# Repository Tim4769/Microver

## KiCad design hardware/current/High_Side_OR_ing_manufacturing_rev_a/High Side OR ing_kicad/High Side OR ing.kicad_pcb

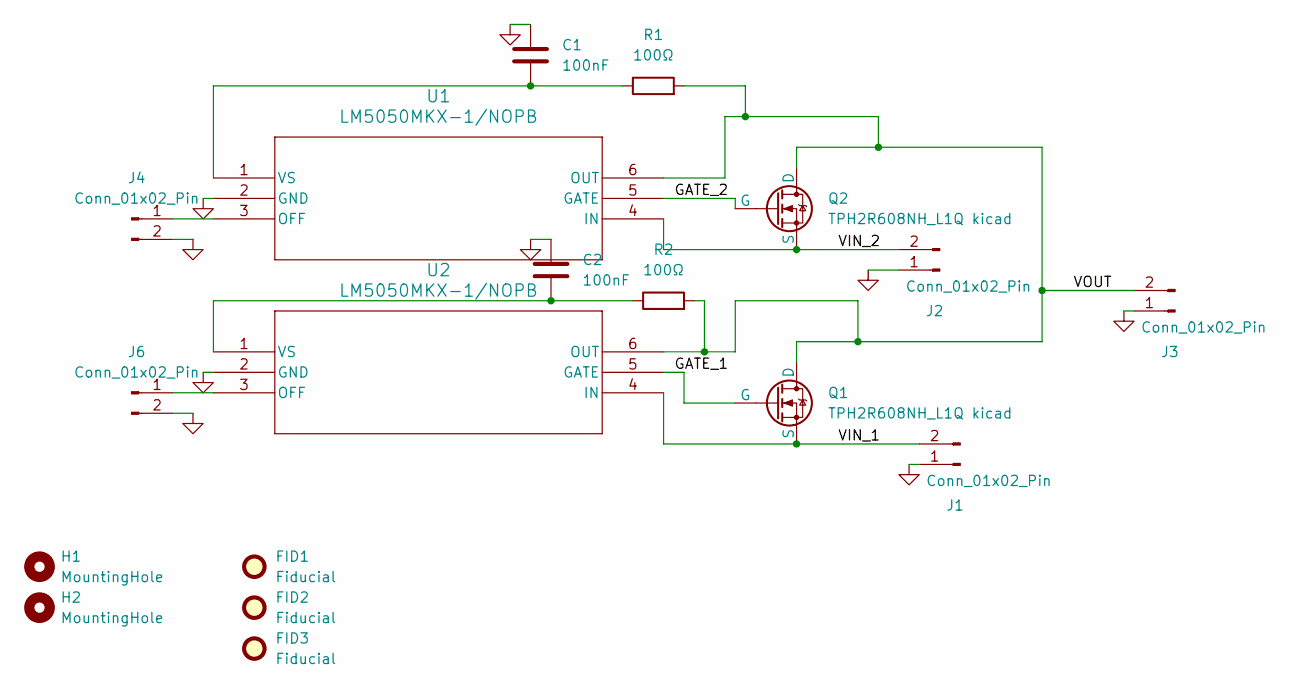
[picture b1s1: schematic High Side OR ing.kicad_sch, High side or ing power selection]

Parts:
C1, C2: 100nF; C_0805_2012Metric; JLCPCB manufactur number C28233
FID1, FID2, FID3: Fiducial; Fiducial_0.5mm_Mask1.5mm
H1, H2: MountingHole; MountingHole_3.2mm_M3
J1, J2, J3: Conn_01x02_Pin; TerminalBlock_MetzConnect_Type011_RT05502HBLC_1x02_P5.00mm_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
J4, J6: Conn_01x02_Pin; PinHeader_1x02_P2.54mm_Vertical
Q1, Q2: TPH2R608NH_L1Q kicad; SOP Advance_TOS; JLCPCB manufactur number C5379811
R1, R2: 100Ω; C_0603_1608Metric; JLCPCB manufactur number C22775
U1, U2: LM5050MKX-1/NOPB; MK06A; JLCPCB manufactur number C473393

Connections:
/GATE_1: Q1.4 (G), U2.5 (GATE)
/GATE_2: Q2.4 (G), U1.5 (GATE)
/VIN_1: J1.2, Q1.1 (S), Q1.2 (S), Q1.3 (S), U2.4 (IN)
/VIN_2: J2.2, Q2.1 (S), Q2.2 (S), Q2.3 (S), U1.4 (IN)
/VOUT: J3.2, Q1.5 (D), Q1.6 (D), Q1.7 (D), Q1.8 (D), Q2.5 (D), Q2.6 (D), Q2.7 (D), Q2.8 (D), R1.2, R2.2, U1.6 (OUT), U2.6 (OUT)
GND: C1.1, C2.1, J1.1, J2.1, J3.1, J4.2, J6.2, U1.2 (GND), U2.2 (GND)
unnamed: J4.1, U1.3 (OFF)
unnamed: J6.1, U2.3 (OFF)
unnamed: C1.2, R1.1, U1.1 (VS)
unnamed: C2.2, R2.1, U2.1 (VS)

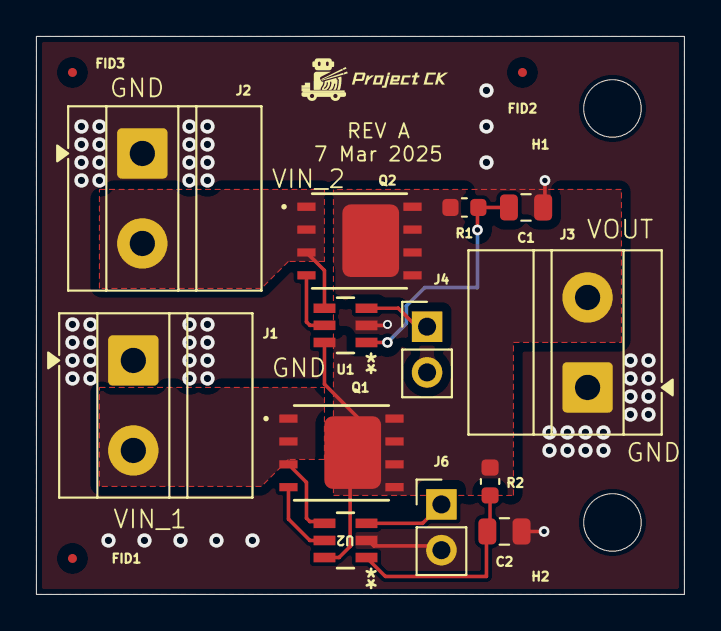
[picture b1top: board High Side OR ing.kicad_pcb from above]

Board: 4 copper layers, 36.0 x 31.0 mm, 18 parts (0 on the bottom side), 10 nets.

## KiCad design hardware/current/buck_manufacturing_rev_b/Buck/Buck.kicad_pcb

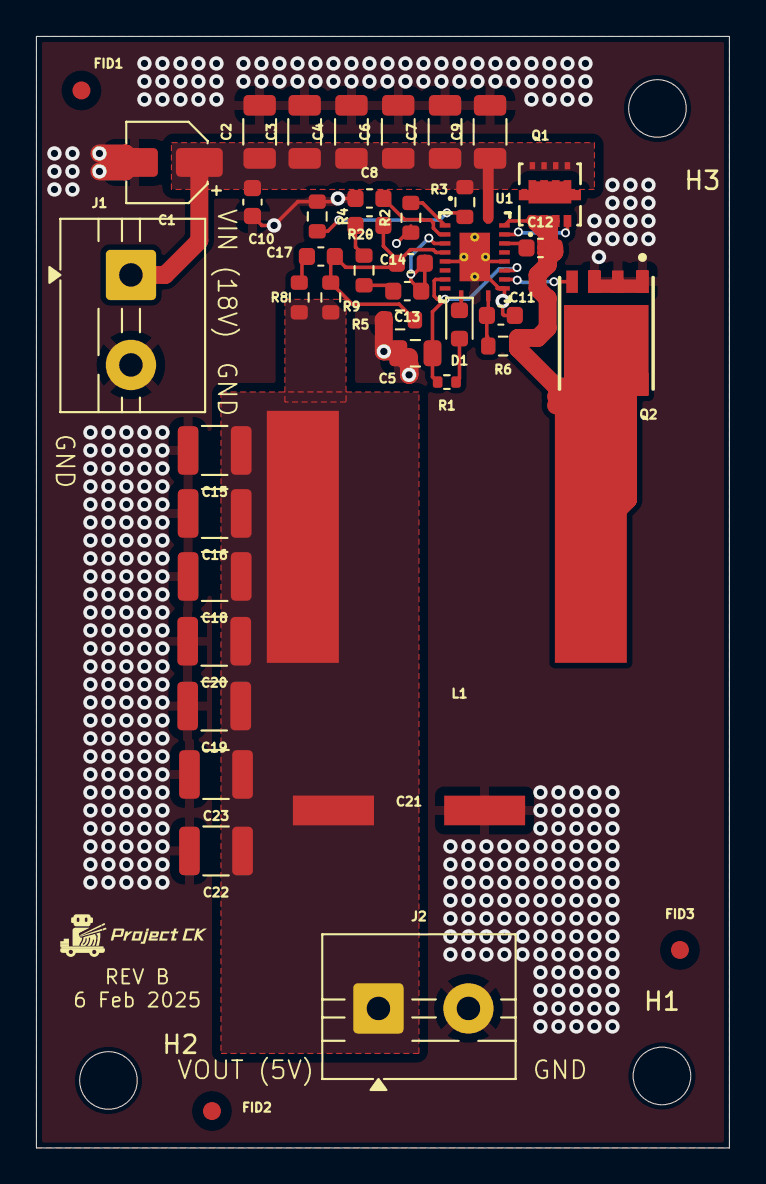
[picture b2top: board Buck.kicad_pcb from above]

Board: 4 copper layers, 38.5 x 61.8 mm, 46 parts (0 on the bottom side), 19 nets.

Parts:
C1: 220 uF; CP_Elec_4x5.4
C2, C3, C4, C6, C7, C9: 4.7 uF; C_1206_3216Metric
C5: 2.2 μF; C_0805_2012Metric
C8: 1uF; C_0603_1608Metric
C10, C12: 0.1 μF; C_0603_1608Metric
C11: 10 pF; C_0603_1608Metric
C13: 4.7nF; C_0603_1608Metric
C14: 68pF; C_0603_1608Metric
C15, C16, C18, C19, C20, C22, C23: 47 μF; C_1210_3225Metric
C17: 2.7nF; C_0603_1608Metric
C21: 680 µF; MA35V680M10X13
D1: R LED; LED_0603_1608Metric
FID1, FID2, FID3: Fiducial; Fiducial_1mm_Mask2mm
H1, H2, H3: MountingHole; MountingHole_3.2mm_M3
J1, J2: Conn_01x02_Socket; TerminalBlock_MaiXu_MX126-5.0-02P_1x02_P5.00mm
L1: 3.3uH; MS1770-3R3M
Q1: NVTFS5C670NLTAG; WDFN8_511AB_ONS
Q2: BSC014N06NS; INF-PG-TDSON-8-FL
R1: 4.7 kΩ; R_0402_1005Metric
R2: 33kΩ; R_0603_1608Metric
R3: 49.9kΩ; R_0603_1608Metric
R4: 4.7kΩ; R_0603_1608Metric
R5: 4.3kΩ; R_0603_1608Metric
R6: 510Ω; R_0603_1608Metric
R7: 7.5 kΩ; R_0603_1608Metric
R8: 430Ω; R_0603_1608Metric
R9: 22kΩ; R_0603_1608Metric
R20: 9.1kΩ; C_0603_1608Metric
U1: LM5146QRGYTQ1; RGY0020B

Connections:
+18V: C1.1, C2.1, C3.1, C4.1, C6.1, C7.1, C9.1, C10.2, J1.1, Q1.5, Q1.6, Q1.7, Q1.8, R3.2, U1.20 (VIN)
/BST: C12.1, U1.17 (BST)
/EN: R3.1, R4.2, U1.1 (EN_UVLO)
/HG: Q1.4, U1.18 (HO)
/ILIM: C11.1, R6.1, U1.11 (ILIM)
/LG: Q2.4 (GATE), U1.13 (LO)
/PGOOD: D1.1 (K), U1.10 (PGOOD)
/RT: R2.2, U1.2 (RT)
/SS: C8.2, U1.3 (SS_TRK)
/SW: C12.2, L1.1, Q1.1, Q1.2, Q1.3, Q2.5 (DRAIN), Q2.6 (DRAIN), Q2.7 (DRAIN), Q2.8 (DRAIN), R6.2, U1.19 (SW)
/SYNCIN: C5.2, R1.1, U1.8 (SYNCIN), U1.14 (VCC)
/VOUT: C15.1, C16.1, C18.1, C19.1, C20.1, C21.1, C22.1, C23.1, J2.1, L1.2, R8.2, R9.2
GND: C1.2, C2.2, C3.2, C4.2, C5.1, C6.2, C7.2, C8.1, C9.2, C10.1, C11.2, C15.2, C16.2, C18.2, C19.2, C20.2, C21.2, C22.2, C23.2, J1.2, J2.2, Q2.1 (SOURCE), Q2.2 (SOURCE), Q2.3 (SOURCE), R2.1, R4.1, R5.2, U1.6 (AGND), U1.12 (PGND), U1.15 (EP), U1.21 (EP)
unnamed: C13.2, R7.1
unnamed: C17.2, R8.1
unnamed: D1.2 (A), R1.2
unnamed: R7.2, R20.1
unnamed: C13.1, C14.1, U1.4 (COMP)
unnamed: C14.2, C17.1, R5.1, R9.1, R20.2, U1.5 (FB)
